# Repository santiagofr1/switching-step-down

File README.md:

# switching-step-down-calibrable
Hecho en KiCad 6.0.0
Basado en Lm2576

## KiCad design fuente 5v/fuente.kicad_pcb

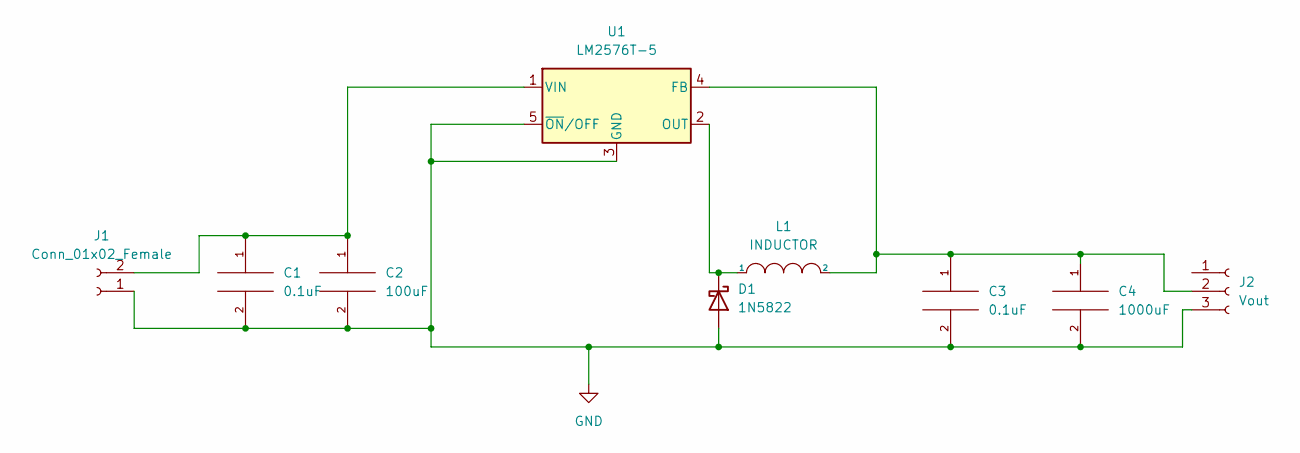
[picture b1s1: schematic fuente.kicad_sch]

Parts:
C1, C3: 0.1uF; C_0805_2012Metric
C2: 100uF; CP_Radial_D8.0mm_P2.50mm
C4: 1000uF; CP_Radial_D10.0mm_P5.00mm
D1: 1N5822; D_DO-201AD_P5.08mm_Vertical_KathodeUp
J1: Conn_01x02_Female; Molex_KK-254_AE-6410-02A_1x02_P2.54mm_Vertical
J2: Vout; Molex_KK-254_AE-6410-03A_1x03_P2.54mm_Vertical
L1: INDUCTOR; L_12x12mm_H6mm
U1: LM2576T-5; TO-220-5_P3.4x3.7mm_StaggerOdd_Lead3.8mm_Vertical

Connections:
GND: C1.2, C2.2, C3.2, C4.2, D1.2 (A), J1.1, J2.3, U1.3 (GND), U1.5 (~ON/OFF)
unnamed: C1.1, C2.1, J1.2, U1.1 (VIN)
unnamed: C3.1, C4.1, J2.2, L1.2, U1.4 (FB)
unnamed: D1.1 (K), L1.1, U1.2 (OUT)

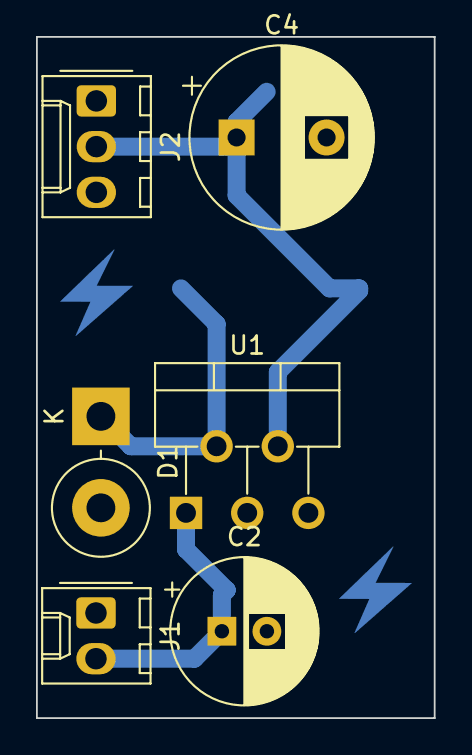
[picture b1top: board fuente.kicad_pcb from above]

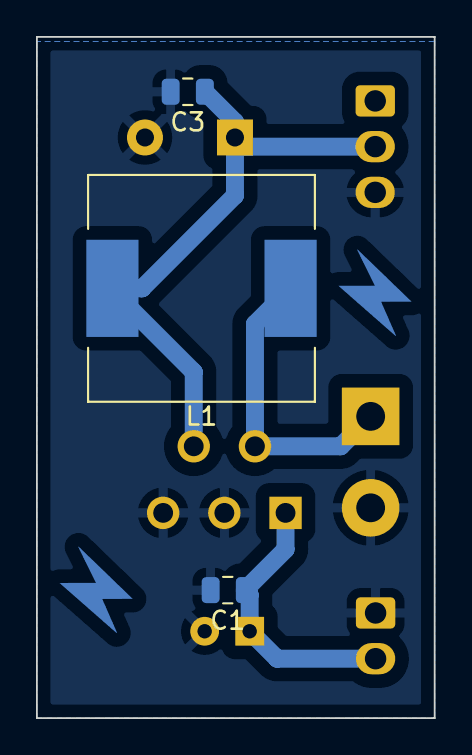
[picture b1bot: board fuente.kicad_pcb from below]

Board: 2 copper layers, 22.1 x 37.8 mm, 9 parts (3 on the bottom side), 4 nets.
